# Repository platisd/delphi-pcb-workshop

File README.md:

# delphi-pcb-workshop
Repository for the Christmas PCB workshop organized at Delphi on 30/11/2017

:evergreen_tree: :evergreen_tree: :evergreen_tree: :evergreen_tree: :evergreen_tree: :evergreen_tree:

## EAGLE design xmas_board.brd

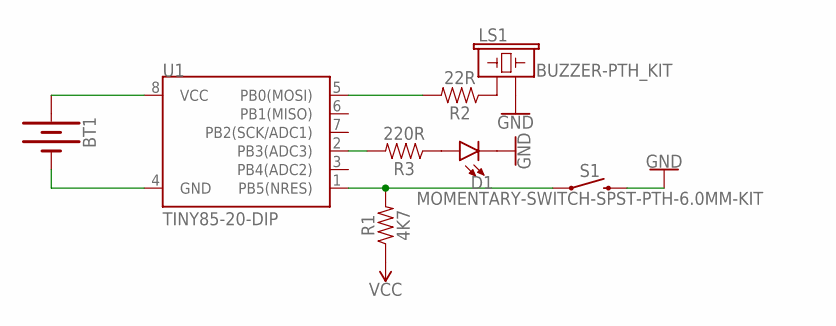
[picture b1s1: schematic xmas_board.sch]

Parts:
BT1: BATTERY-20MM_PTH; BATTCOM_20MM_PTH
D1: LED5MM-KIT; LED_5MM-KIT
LS1: BUZZER-PTH_KIT; BUZZER-12MM-KIT
R1: 4K7; AXIAL-0.3-KIT
R2: 22R; AXIAL-0.3-KIT
R3: 220R; AXIAL-0.3-KIT
S1: MOMENTARY-SWITCH-SPST-PTH-6.0MM-KIT; TACTILE_SWITCH_PTH_6.0MM_KIT
U1: TINY85-20-DIP; DIP08_MCU

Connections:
GND: D1.K (C), LS1.- (2), S1.3 (2)
unnamed: R1.P$2 (2), S1.1, U1.1 (PB5(NRES))
unnamed: R2.P$2 (2), U1.5 (PB0(MOSI))
unnamed: LS1.+ (1), R2.P$1 (1)
unnamed: BT1.1 (+), U1.8 (VCC)
unnamed: BT1.2 (-), U1.4 (GND)
unnamed: D1.A, R3.P$1 (1)
unnamed: R3.P$2 (2), U1.2 (PB3(ADC3))
VCC: R1.P$1 (1)

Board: 2 copper layers, 8 parts (0 on the bottom side), 8 nets, no tracks yet.

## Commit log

2017-11-28 Add sample christmas board :evergreen_tree:
    It's a Christmas tree!
2017-11-28 Moved PCB files to hardware folder
2017-11-28 Add ringtone melody playing sketch
2017-11-28 Add many :evergreen_tree:
2017-11-29 Add eagle project file to ignore list
2017-11-29 Add manufacturing files

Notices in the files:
parts and their libraries:
SparkFun-Retired: Licensing: Creative Commons ShareAlike 4.0 International - https://creativecommons.org/licenses/by-sa/4.0
